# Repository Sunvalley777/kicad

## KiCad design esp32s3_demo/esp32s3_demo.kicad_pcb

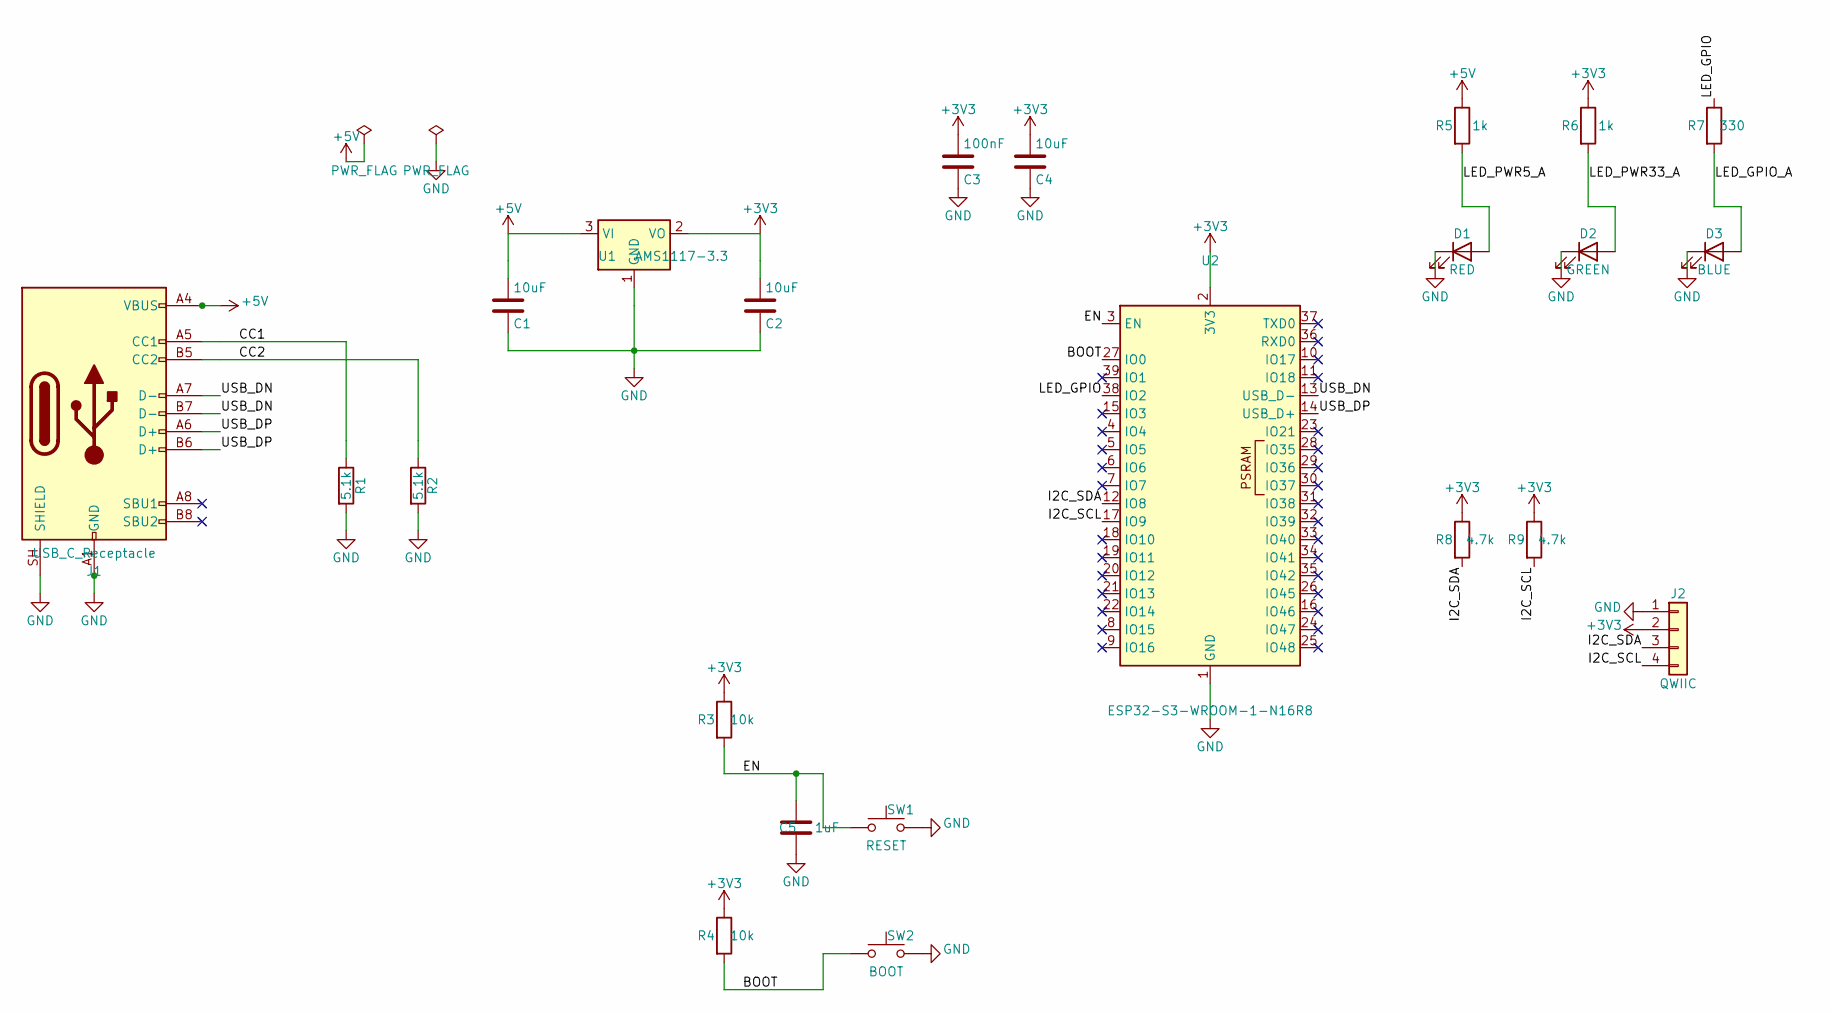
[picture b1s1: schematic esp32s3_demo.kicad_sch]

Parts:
C1, C2, C4: 10uF; C_0603_1608Metric
C3: 100nF; C_0603_1608Metric
C5: 1uF; C_0603_1608Metric
D1: RED; LED_0603_1608Metric
D2: GREEN; LED_0603_1608Metric
D3: BLUE; LED_0603_1608Metric
J1: USB_C_Receptacle; USB_C_Receptacle_HRO_TYPE-C-31-M-12
J2: QWIIC; JST_SH_SM04B-SRSS-TB_1x04-1MP_P1.00mm_Horizontal
R1, R2: 5.1k; R_0603_1608Metric
R3, R4: 10k; R_0603_1608Metric
R5, R6: 1k; R_0603_1608Metric
R7: 330; R_0603_1608Metric
R8, R9: 4.7k; R_0603_1608Metric
SW1: RESET; SW_SPST_TL3342
SW2: BOOT; SW_SPST_TL3342
U1: AMS1117-3.3; SOT-223-3_TabPin2
U2: ESP32-S3-WROOM-1-N16R8; ESP32-S3-WROOM-1

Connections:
+3V3: C2.1, C3.1, C4.1, J2.2, R3.1, R4.1, R6.1, R8.1, R9.1, U1.2 (VO), U2.2 (3V3)
+5V: C1.1, J1.A4 (VBUS), J1.A9 (VBUS), J1.B4 (VBUS), J1.B9 (VBUS), R5.1, U1.3 (VI)
/BOOT: R4.2, SW2.1, U2.27 (IO0)
/CC1: J1.A5 (CC1), R1.1
/CC2: J1.B5 (CC2), R2.1
/EN: C5.1, R3.2, SW1.1, U2.3 (EN)
/I2C_SCL: J2.4, R9.2, U2.17 (IO9)
/I2C_SDA: J2.3, R8.2, U2.12 (IO8)
/LED_GPIO: R7.1, U2.38 (IO2)
/LED_GPIO_A: D3.2 (A), R7.2
/LED_PWR5_A: D1.2 (A), R5.2
/LED_PWR33_A: D2.2 (A), R6.2
/USB_DN: J1.A7 (D-), J1.B7 (D-), U2.13 (USB_D-)
/USB_DP: J1.A6 (D+), J1.B6 (D+), U2.14 (USB_D+)
GND: C1.2, C2.2, C3.2, C4.2, C5.2, D1.1 (K), D2.1 (K), D3.1 (K), J1.A1 (GND), J1.A12 (GND), J1.B1 (GND), J1.B12 (GND), J1.SH (SHIELD), J2.1, R1.2, R2.2, SW1.2, SW2.2, U1.1 (GND), U2.1 (GND), U2.40 (GND), U2.41 (GND)

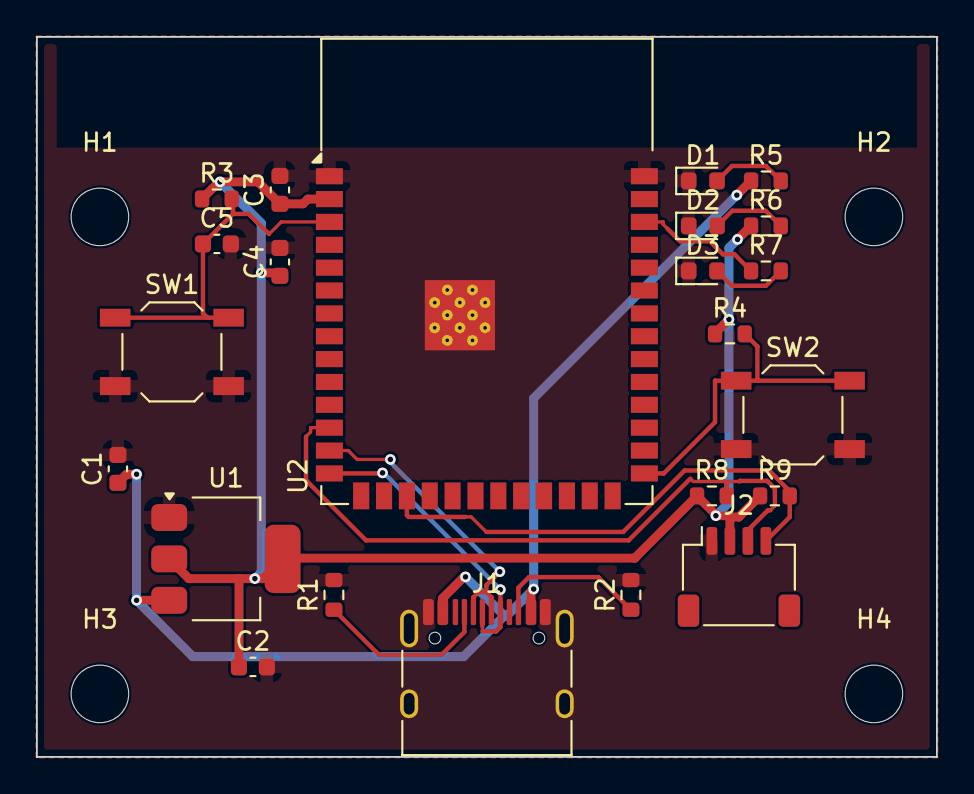
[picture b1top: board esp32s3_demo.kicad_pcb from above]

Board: 2 copper layers, 50.0 x 40.0 mm, 27 parts (0 on the bottom side), 15 nets.

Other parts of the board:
H1, H2, H3, H4: MountingHole_3.2mm_M3
